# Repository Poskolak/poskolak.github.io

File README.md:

# poskolak.github.io
Repozitář pro GitHub stránky kroužku robotiky

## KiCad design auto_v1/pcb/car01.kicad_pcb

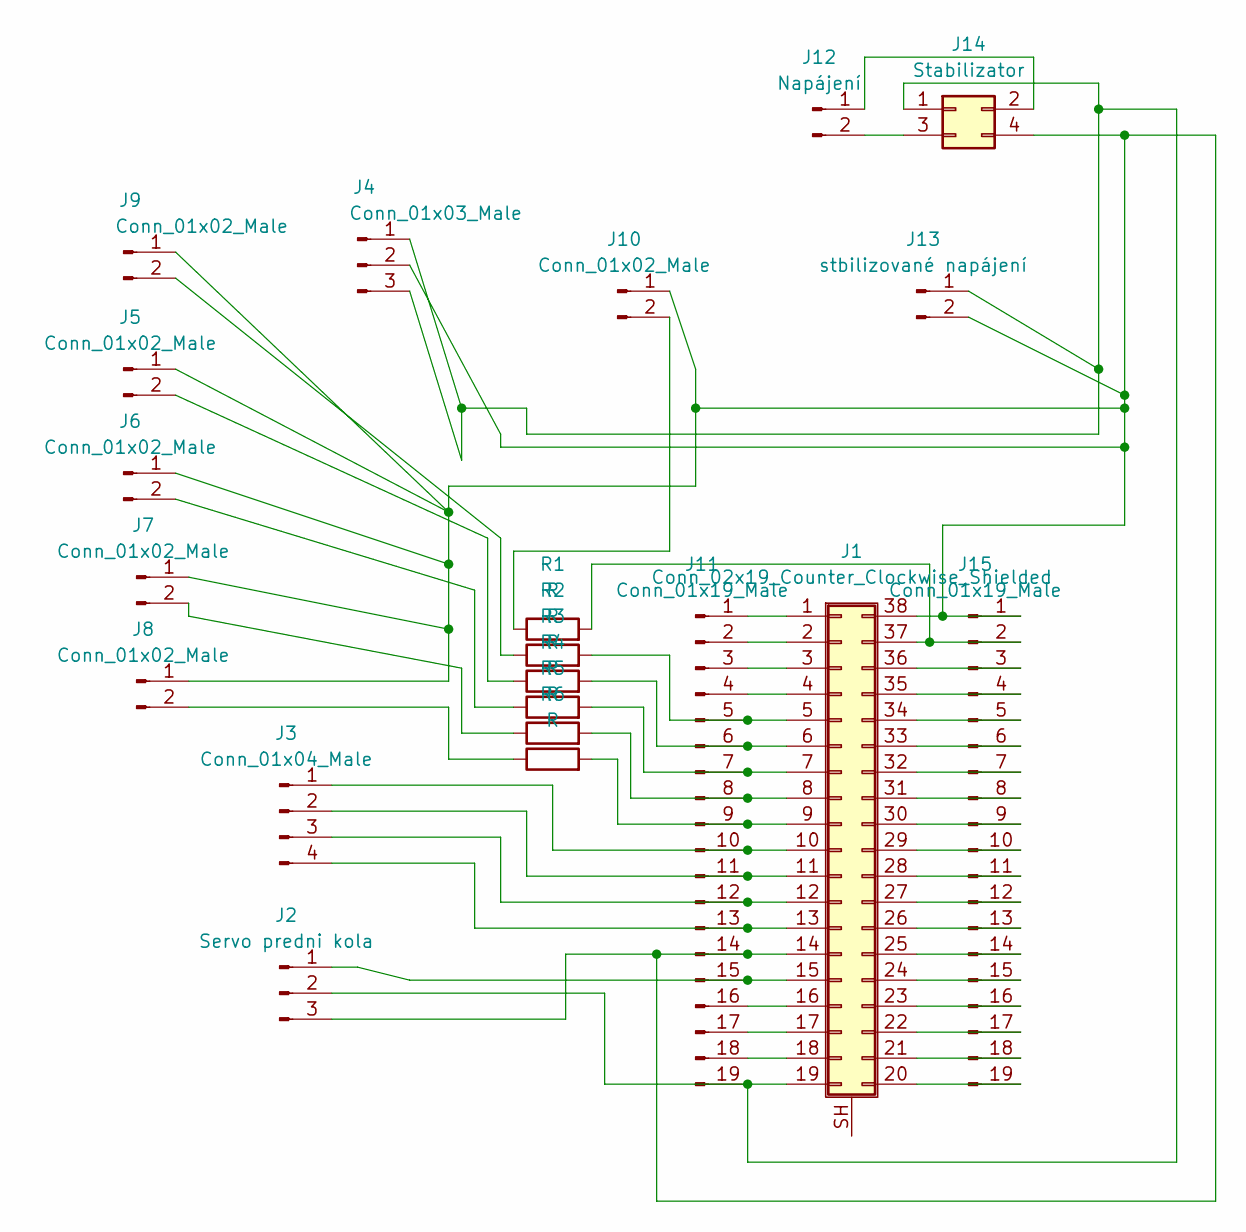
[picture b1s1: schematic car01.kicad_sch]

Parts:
J1: Conn_02x19_Counter_Clockwise_Shielded; ESP32
J2: Servo predni kola; PinHeader_1x03_P2.54mm_Vertical
J3: Conn_01x04_Male; PinHeader_1x04_P2.54mm_Vertical
J4: Conn_01x03_Male; JST_EH_B3B-EH-A_1x03_P2.50mm_Vertical
J5, J6, J7, J8, J9, J10: Conn_01x02_Male; JST_EH_B2B-EH-A_1x02_P2.50mm_Vertical
J11, J15: Conn_01x19_Male; PinHeader_1x19_P2.54mm_Vertical
J12: Napájení; JST_EH_B2B-EH-A_1x02_P2.50mm_Vertical
J13: stbilizované napájení; JST_EH_B2B-EH-A_1x02_P2.50mm_Vertical
J14: Stabilizator; StepUp
R1, R2, R3, R4, R5, R6: R; R_Axial_DIN0411_L9.9mm_D3.6mm_P12.70mm_Horizontal

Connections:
unnamed: J1.1, J11.1
unnamed: J1.2, J11.2
unnamed: J1.3, J11.3
unnamed: J1.4, J11.4
unnamed: J1.5, J11.5, R2.2
unnamed: J1.6, J11.6, R3.2
unnamed: J1.7, J11.7, R4.2
unnamed: J1.8, J11.8, R5.2
unnamed: J1.9, J11.9, R6.2
unnamed: J1.10, J3.1, J11.10
unnamed: J1.11, J3.2, J11.11
unnamed: J1.12, J3.3, J11.12
unnamed: J1.13, J3.4, J11.13
unnamed: J1.14, J1.38, J2.3, J4.2, J5.1, J6.1, J7.1, J8.1, J9.1, J10.1, J11.14, J13.2, J14.4, J15.1
unnamed: J1.15, J2.1, J11.15
unnamed: J1.16, J11.16
unnamed: J1.17, J11.17
unnamed: J1.18, J11.18
unnamed: J1.19, J2.2, J4.1, J4.3, J11.19, J13.1, J14.1
unnamed: J1.20, J15.19
unnamed: J1.21, J15.18
unnamed: J1.22, J15.17
unnamed: J1.23, J15.16
unnamed: J1.24, J15.15
unnamed: J1.25, J15.14
unnamed: J1.26, J15.13
unnamed: J1.27, J15.12
unnamed: J1.28, J15.11
unnamed: J1.29, J15.10
unnamed: J1.30, J15.9
unnamed: J1.31, J15.8
unnamed: J1.32, J15.7
unnamed: J1.33, J15.6
unnamed: J1.34, J15.5
unnamed: J1.35, J15.4
unnamed: J1.36, J15.3
unnamed: J1.37, J15.2, R1.2
unnamed: J5.2, R3.1
unnamed: J6.2, R4.1
unnamed: J7.2, R5.1
unnamed: J8.2, R6.1
unnamed: J9.2, R2.1
unnamed: J10.2, R1.1
unnamed: J12.1, J14.2
unnamed: J12.2, J14.3

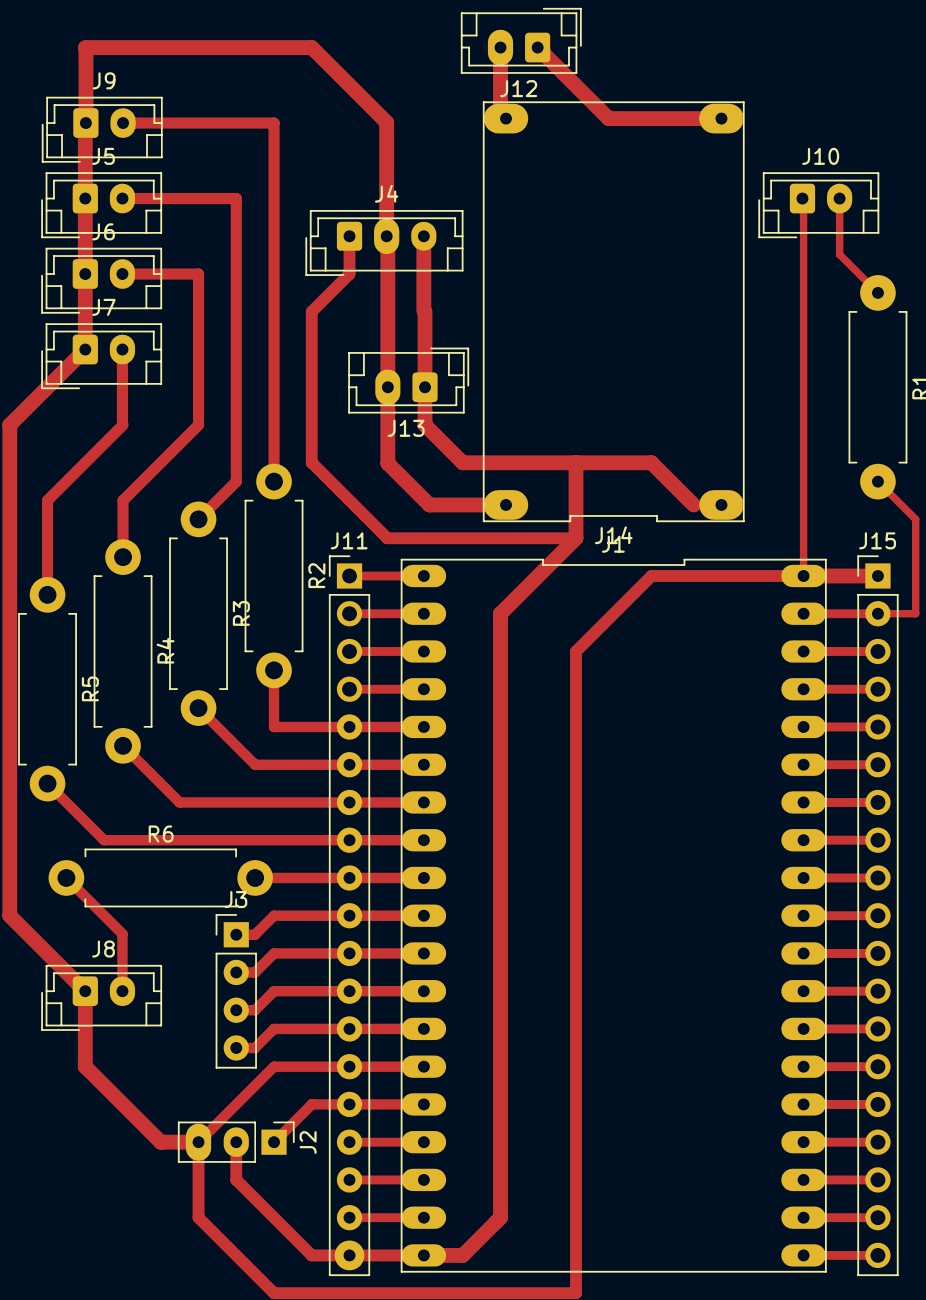
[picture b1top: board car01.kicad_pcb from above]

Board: 2 copper layers, 21 parts (0 on the bottom side), 45 nets.

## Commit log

2020-10-02 Set theme jekyll-theme-minimal
2020-10-02 Úvodní stránky vytvořená šablonou
2020-10-02 Informace k úvodnímu kroužku 2.10.
2020-10-09 Nařízení vlády
2021-12-17 Create pokus
2021-12-17 Rename pokus to pokus.md
2022-01-07 Vymazání Markdown souborů
2022-01-08 Úkoly 7.1.
2022-01-20 hahaha
2022-01-27 Create nelinkaChaty
2022-01-27 Rename nelinkaChaty to nelinkaChaty.html
2022-03-11 Create michal-chats.html
    Credit: https://www.cometchat.com/tutorials/how-to-build-a-chat-app-with-firebase
2022-03-11 Dokončení Michalovo chatu
2022-03-11 Úprava indexu
2022-05-20 Podklady pro RC auto
2022-06-17 vizualizace auta
